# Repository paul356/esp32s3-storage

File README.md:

# esp32s3-storage

这是一款基于ESP32S3的移动存储产品的PCB板，这个开源硬件项目使用开源软件KiCad8打开esp32s3-storage.kicad<sub>pro文件来浏览和修改</sub>。项目基于GPLv3，本项目不提供任何保证，但允许任意修改，但需要保持开源义务。欢迎大家提Issue或PR。

本项目使用了两个需要引入的元器件。第一个是micro-sd的封装文件new-micro-sd-socket-taobao-9-pin.kicad<sub>mod</sub>，位于项目目录中，使用footprint editor导入该文件，创建的库名是imported-footprint，footprint名字是new-micro-sd-socket-taobao-9-pin。另一个元器件是ESP32S3，通过安装espressif-kicad-addon插件获得该元器件。通过乐鑫[kicad-libraries](https://github.com/espressif/kicad-libraries)项目页面下载插件包，再打开KiCad8的Plugin and Content Manager工具，点击Install from File&#x2026;，选中下载好的插件文件，安装插件。安装好后会在Installed Tab页看到Espressif Libary。

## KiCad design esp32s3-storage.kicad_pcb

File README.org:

* esp32s3-storage

这是一款基于ESP32S3的移动存储产品的PCB板，这个开源硬件项目使用开源软件KiCad8打开esp32s3-storage.kicad_pro文件来浏览和修改。项目基于GPLv3，本项目不提供任何保证，但允许任意修改，但需要保持开源义务。欢迎大家提Issue或PR。

本项目使用了两个需要引入的元器件。第一个是micro-sd的封装文件new-micro-sd-socket-taobao-9-pin.kicad_mod，位于项目目录中，使用footprint editor导入该文件，创建的库名是imported-footprint，footprint名字是new-micro-sd-socket-taobao-9-pin。另一个元器件是ESP32S3，通过安装espressif-kicad-addon插件获得该元器件。通过乐鑫[[https://github.com/espressif/kicad-libraries][kicad-libraries]]项目页面下载插件包，再打开KiCad8的Plugin and Content Manager工具，点击Install from File...，选中下载好的插件文件，安装插件。安装好后会在Installed Tab页看到Espressif Libary。

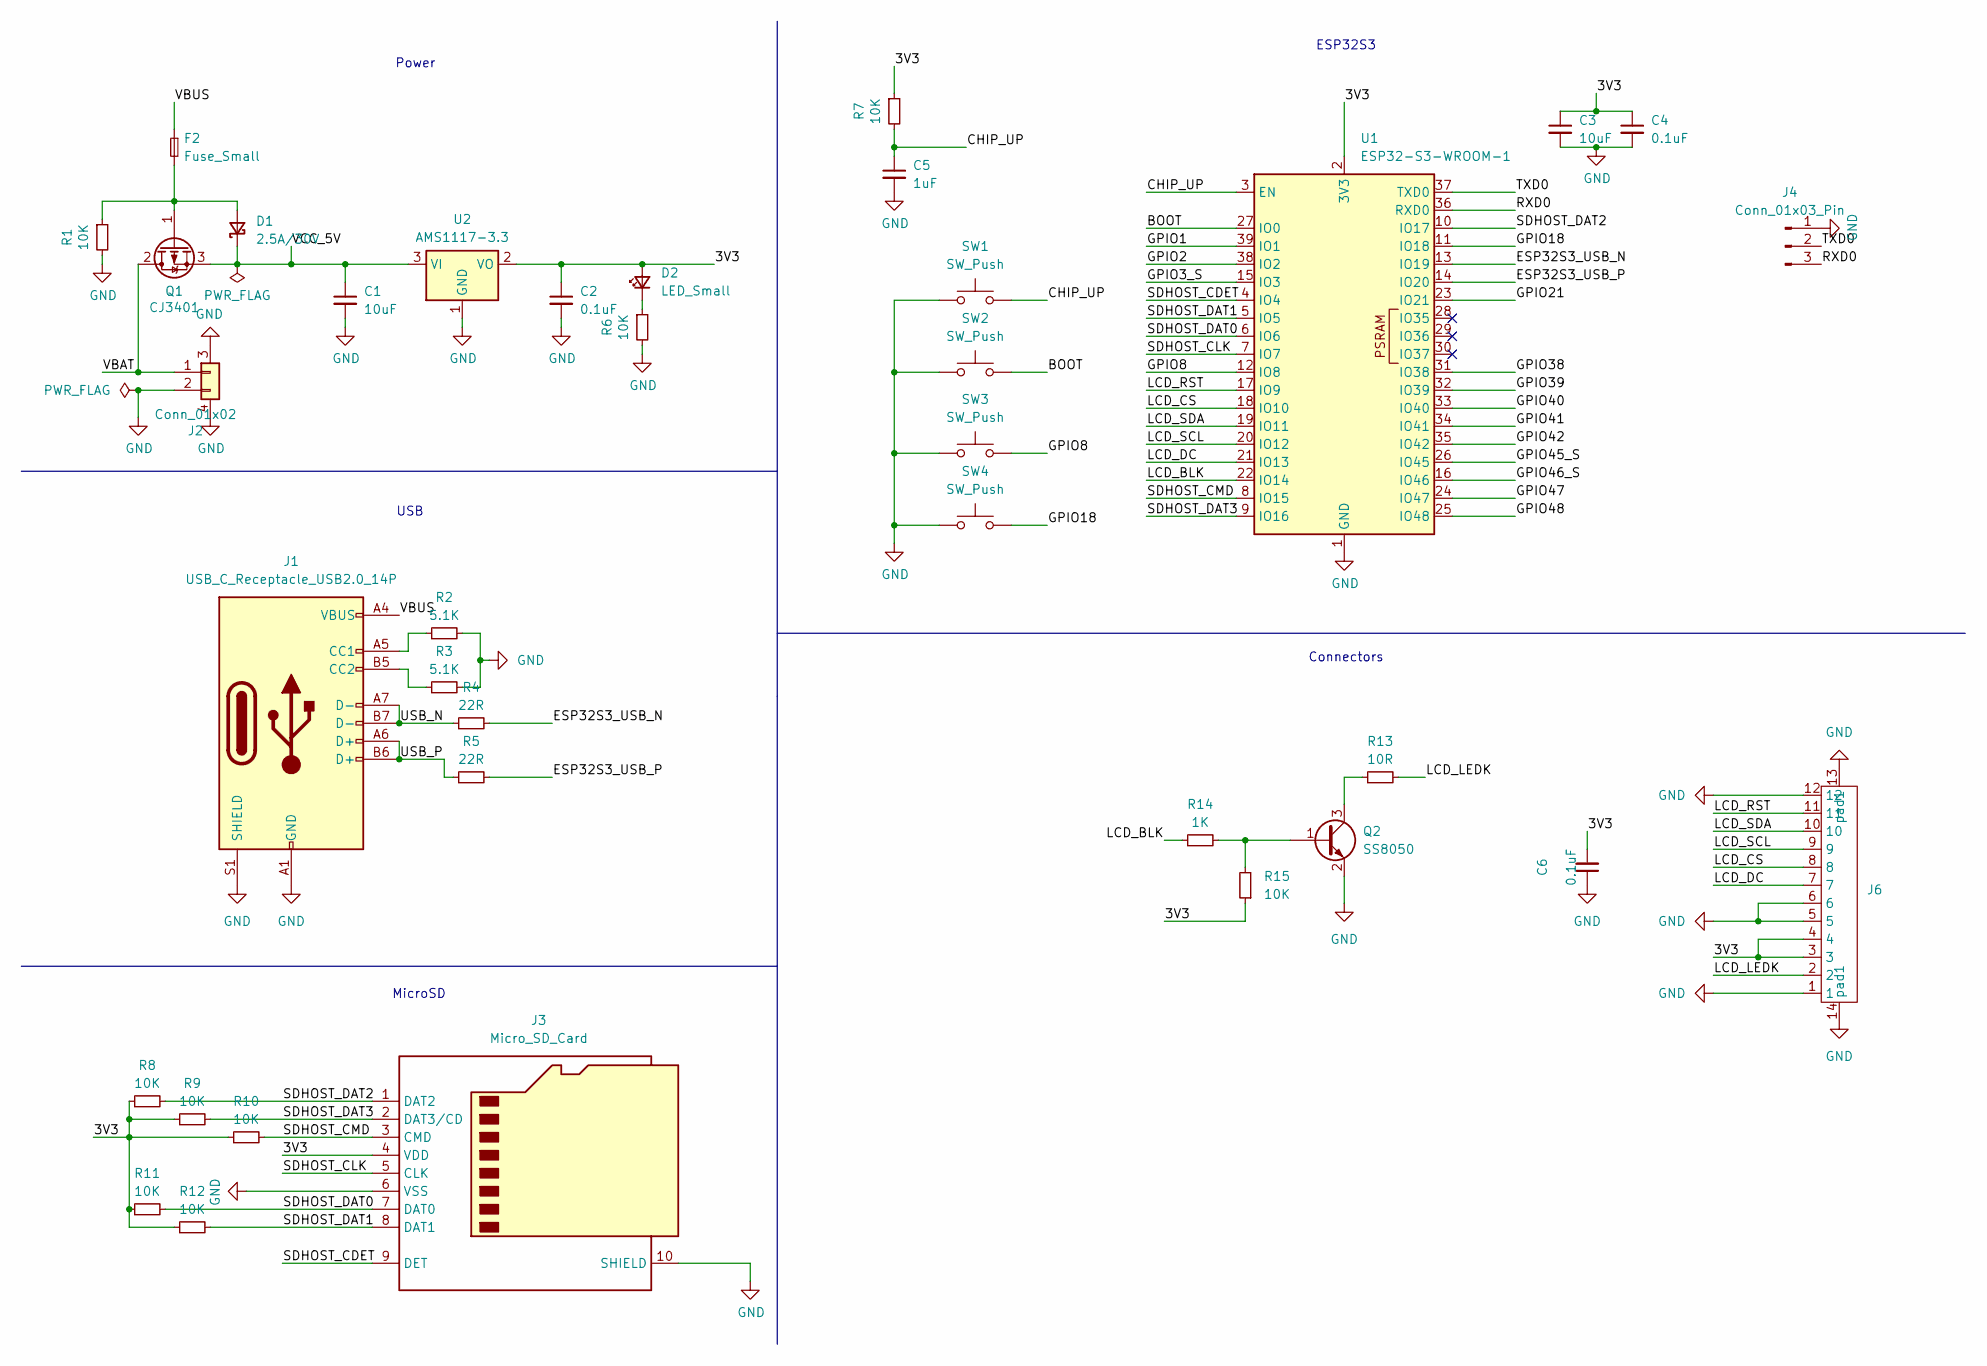
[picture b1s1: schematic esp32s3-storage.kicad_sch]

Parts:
C1, C3: 10uF; C_0603_1608Metric; LCSC Part # C19702
C2, C4, C6: 0.1uF; C_0603_1608Metric; LCSC Part # C14663
C5: 1uF; C_0603_1608Metric; LCSC Part # C15849
D1: 2.5A/30V; D_SOD-123; LCSC Part # C8598
D2: LED_Small; LED_0603_1608Metric; LCSC Part # C2286
F2: Fuse_Small; Fuse_0805_2012Metric; LCSC Part # C3161772
J1: USB_C_Receptacle_USB2.0_14P; USB_C_Receptacle_HRO_TYPE-C-31-M-12; LCSC Part # C2988369
J2: Conn_01x02; 1x2 pin gap 1.25mm SMD socket; LCSC Part # C2845379
J3: Micro_SD_Card; new-micro-sd-socket-taobao-9-pin; LCSC Part # C381082
J4: Conn_01x03_Pin; PinHeader_1x03_P2.54mm_Vertical
J6: JST AFC01-S12FCC-00 1x2 P0.5mm back-flip bottom-side; LCSC Part # C262268
Q1: CJ3401; SOT-23; LCSC Part # C15127
Q2: SS8050; SOT-23; LCSC Part # C2150
R1, R6, R7, R8, R9, R10, R11, R12, R15: 10K; R_0603_1608Metric; LCSC Part # C25804
R2, R3: 5.1K; R_0603_1608Metric; LCSC Part # C23186
R4, R5: 22R; R_0603_1608Metric; LCSC Part # C23345
R13: 10R; R_0603_1608Metric
R14: 1K; R_0603_1608Metric
SW1, SW2, SW3, SW4: SW_Push; SW_SPST_PTS647_Sx38; LCSC Part # C318884
U1: ESP32-S3-WROOM-1; LCSC Part # C2913204
U2: AMS1117-3.3; SOT-223-3_TabPin2; LCSC Part # C6186

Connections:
/3V3: C2.1, C3.1, C4.1, C6.2, D2.2 (A), J3.4 (VDD), J6.3, J6.4, R7.1, R8.1, R9.1, R10.1, R11.1, R12.1, R15.1, U1.2 (3V3), U2.2 (VO)
/BOOT: SW2.2, U1.27 (IO0)
/CHIP_UP: C5.1, R7.2, SW1.2, U1.3 (EN)
/ESP32S3_USB_N: R4.2, U1.13 (IO19)
/ESP32S3_USB_P: R5.2, U1.14 (IO20)
/GPIO1: U1.39 (IO1)
/GPIO2: U1.38 (IO2)
/GPIO3_S: U1.15 (IO3)
/GPIO8: SW3.2, U1.12 (IO8)
/GPIO18: SW4.2, U1.11 (IO18)
/GPIO21: U1.23 (IO21)
/GPIO38: U1.31 (IO38)
/GPIO39: U1.32 (IO39)
/GPIO40: U1.33 (IO40)
/GPIO41: U1.34 (IO41)
/GPIO42: U1.35 (IO42)
/GPIO45_S: U1.26 (IO45)
/GPIO46_S: U1.16 (IO46)
/GPIO47: U1.24 (IO47)
/GPIO48: U1.25 (IO48)
/LCD_BLK: R14.1, U1.22 (IO14)
/LCD_CS: J6.8, U1.18 (IO10)
/LCD_DC: J6.7, U1.21 (IO13)
/LCD_LEDK: J6.2, R13.2
/LCD_RST: J6.11, U1.17 (IO9)
/LCD_SCL: J6.9, U1.20 (IO12)
/LCD_SDA: J6.10, U1.19 (IO11)
/RXD0: J4.3, U1.36 (RXD0)
/SDHOST_CDET: J3.9 (DET), U1.4 (IO4)
/SDHOST_CLK: J3.5 (CLK), U1.7 (IO7)
/SDHOST_CMD: J3.3 (CMD), R10.2, U1.8 (IO15)
/SDHOST_DAT0: J3.7 (DAT0), R11.2, U1.6 (IO6)
/SDHOST_DAT1: J3.8 (DAT1), R12.2, U1.5 (IO5)
/SDHOST_DAT2: J3.1 (DAT2), R8.2, U1.10 (IO17)
/SDHOST_DAT3: J3.2 (DAT3/CD), R9.2, U1.9 (IO16)
/TXD0: J4.2, U1.37 (TXD0)
/USB_N: J1.A7 (D-), J1.B7 (D-), R4.1
/USB_P: J1.A6 (D+), J1.B6 (D+), R5.1
/VBAT: J2.1, Q1.2 (D)
/VBUS: F2.1, J1.A4 (VBUS), J1.A9 (VBUS), J1.B4 (VBUS), J1.B9 (VBUS)
/VCC_5V: C1.1, D1.1 (K), Q1.3 (S), U2.3 (VI)
GND: C1.2, C2.2, C3.2, C4.2, C5.2, C6.1, J1.A1 (GND), J1.A12 (GND), J1.B1 (GND), J1.B12 (GND), J1.S1 (SHIELD), J2.2, J2.3, J2.4, J3.6 (VSS), J3.10 (SHIELD), J4.1, J6.1, J6.5, J6.6, J6.12, J6.13 (pad1), J6.14 (pad1), Q2.2 (E), R1.2, R2.2, R3.2, R6.2, SW1.1, SW2.1, SW3.1, SW4.1, U1.1 (GND), U1.40 (GND), U1.41 (GND), U2.1 (GND)
unnamed: D1.2 (A), F2.2, Q1.1 (G), R1.1
unnamed: D2.1 (K), R6.1
unnamed: J1.A5 (CC1), R2.1
unnamed: J1.B5 (CC2), R3.1
unnamed: Q2.1 (B), R14.2, R15.2
unnamed: Q2.3 (C), R13.1

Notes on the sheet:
USB
Connectors
MicroSD
ESP32S3
Power

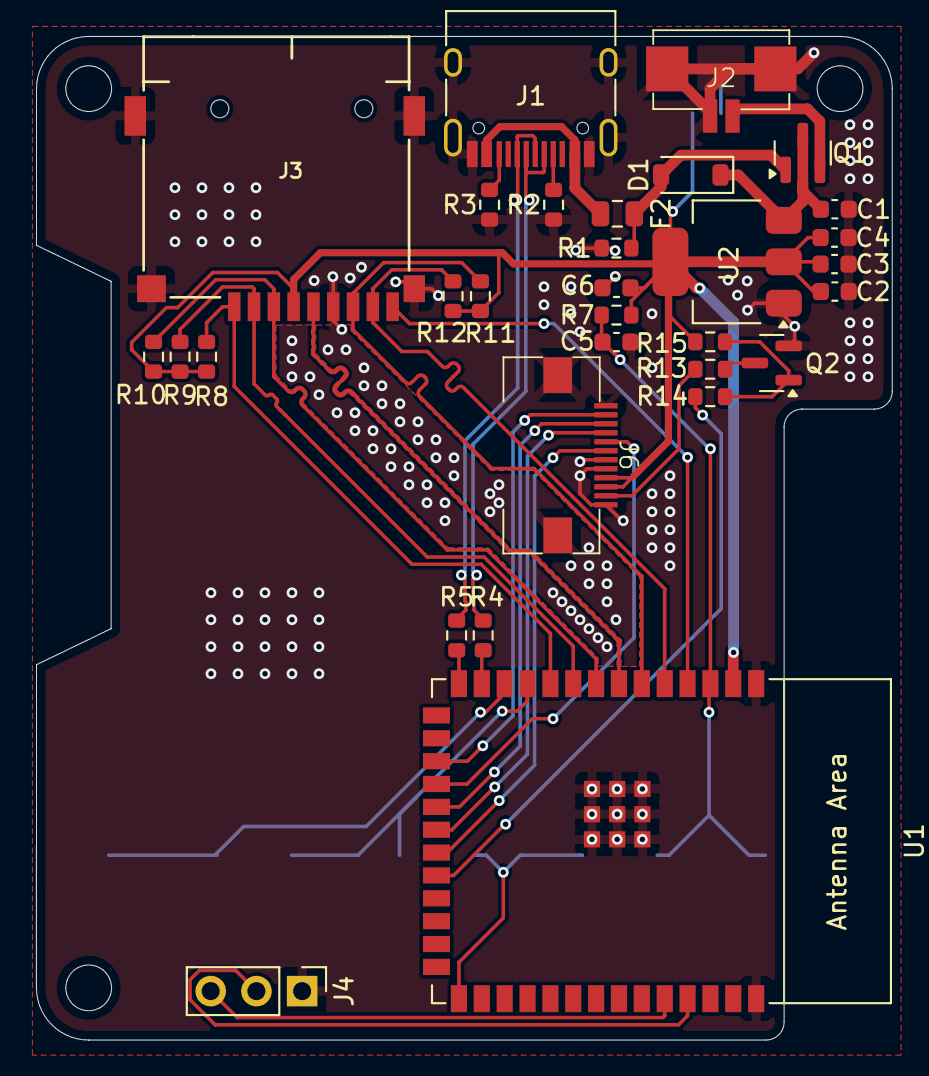
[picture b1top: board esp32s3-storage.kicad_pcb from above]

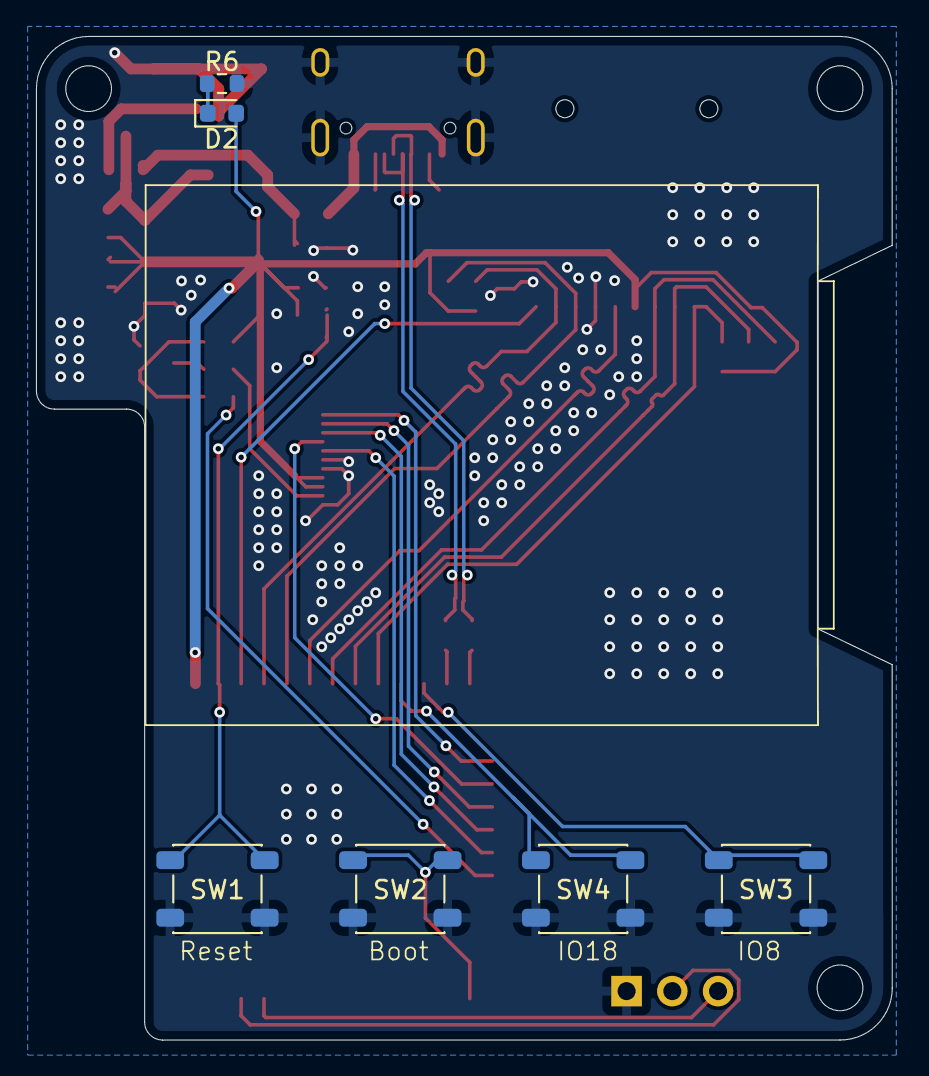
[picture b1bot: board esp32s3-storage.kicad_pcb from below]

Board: 2 copper layers, 47.5 x 55.8 mm, 37 parts (6 on the bottom side), 35 nets.

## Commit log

2024-12-16 baseline for esp32-storage version 0.1
2024-12-16 Add readme and license file
2025-01-21 begin modify pcb layout
2025-01-23 The second version of esp32s3 storage. Becare of the SDIO pins which are changed!
2025-01-23 add silk to switches
2025-03-12 esp32s3-storage v3
2025-03-21 esp32s3-storage v4
2025-04-01 esp32s3-storage v5
2025-04-01 Reposition two value texts on the paste layer
2025-04-01 Add the sn for fpc socket
2025-04-02 Update sn for type-c socket and fuse
2025-04-02 add sn for fuse and type-c usb
